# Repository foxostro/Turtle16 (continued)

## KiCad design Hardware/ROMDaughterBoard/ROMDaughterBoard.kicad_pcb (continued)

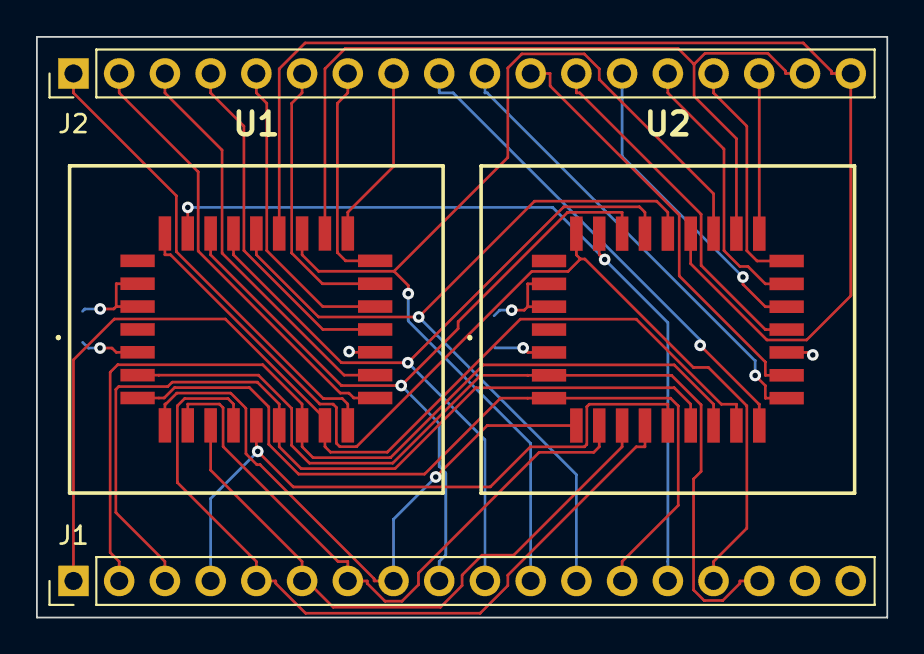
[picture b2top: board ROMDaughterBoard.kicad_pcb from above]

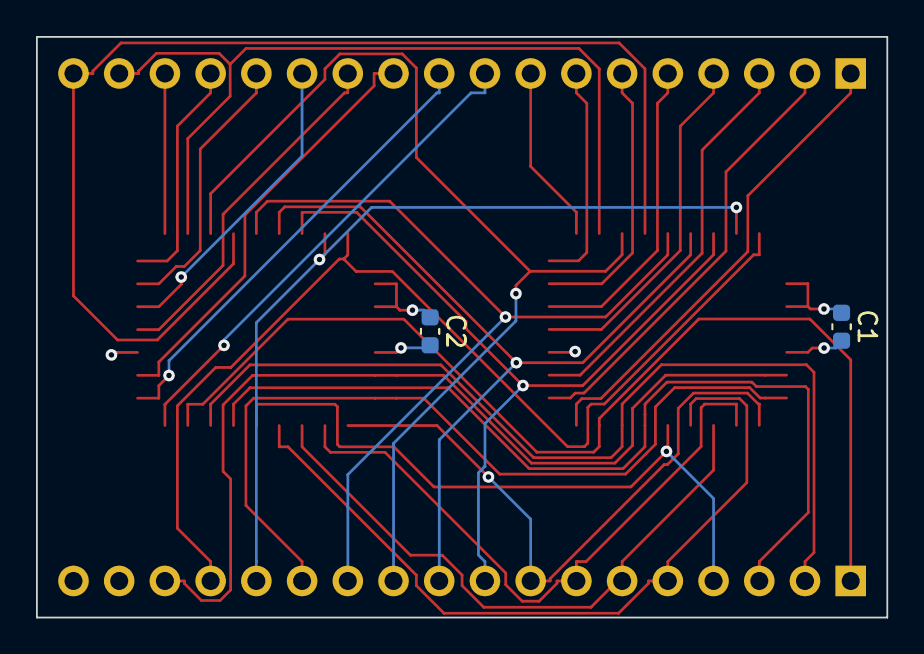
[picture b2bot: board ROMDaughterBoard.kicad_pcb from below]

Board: 4 copper layers, 47.2 x 32.3 mm, 6 parts (2 on the bottom side), 36 nets.

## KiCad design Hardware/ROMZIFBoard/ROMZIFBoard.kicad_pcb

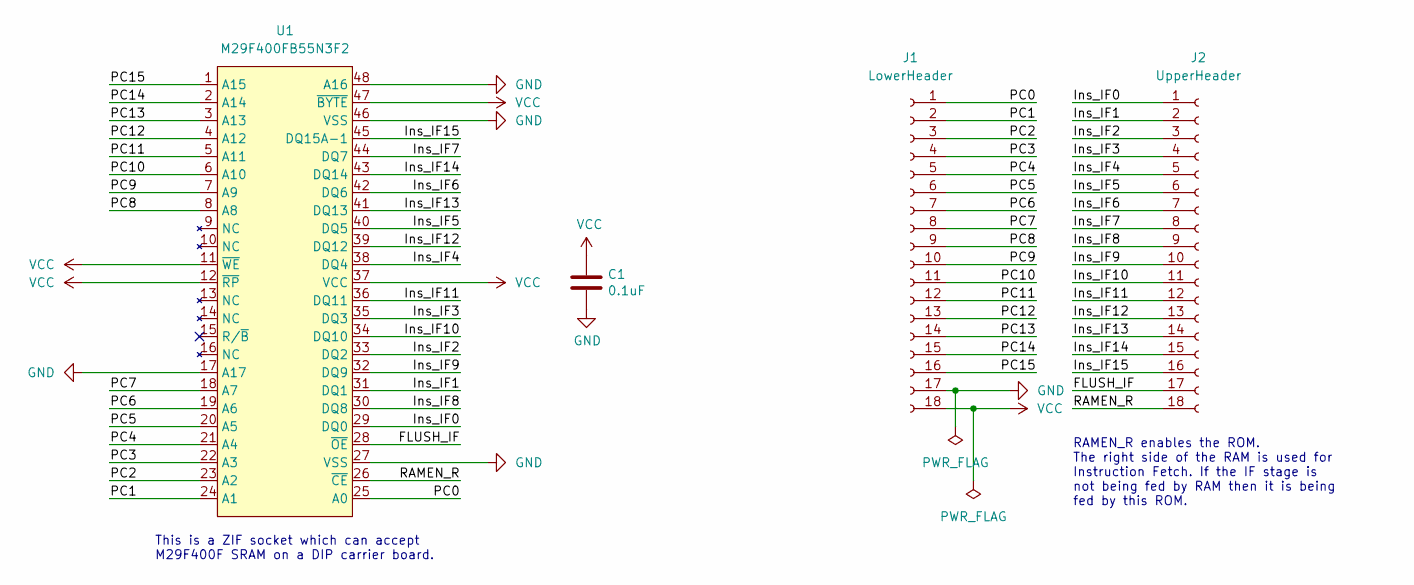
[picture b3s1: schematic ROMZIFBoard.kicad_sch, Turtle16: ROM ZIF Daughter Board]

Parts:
C1: 0.1uF; C_0603_1608Metric; Manufacturer# EMK107B7104KAHT; Mouser# 963-EMK107B7104KAHT
J1: LowerHeader; PinSocket_1x18_P2.54mm_Vertical
J2: UpperHeader; PinSocket_1x18_P2.54mm_Vertical
U1: M29F400FB55N3F2; DIP-48_W15.24mm_Socket; Manufacturer# 48-6554-10; Mouser# 535-48-6554-10

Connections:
/FLUSH_IF: J2.17, U1.28 (~OE)
/Ins_IF0: J2.1, U1.29 (DQ0)
/Ins_IF1: J2.2, U1.31 (DQ1)
/Ins_IF2: J2.3, U1.33 (DQ2)
/Ins_IF3: J2.4, U1.35 (DQ3)
/Ins_IF4: J2.5, U1.38 (DQ4)
/Ins_IF5: J2.6, U1.40 (DQ5)
/Ins_IF6: J2.7, U1.42 (DQ6)
/Ins_IF7: J2.8, U1.44 (DQ7)
/Ins_IF8: J2.9, U1.30 (DQ8)
/Ins_IF9: J2.10, U1.32 (DQ9)
/Ins_IF10: J2.11, U1.34 (DQ10)
/Ins_IF11: J2.12, U1.36 (DQ11)
/Ins_IF12: J2.13, U1.39 (DQ12)
/Ins_IF13: J2.14, U1.41 (DQ13)
/Ins_IF14: J2.15, U1.43 (DQ14)
/Ins_IF15: J2.16, U1.45 (DQ15A-1)
/PC0: J1.1, U1.25 (A0)
/PC1: J1.2, U1.24 (A1)
/PC2: J1.3, U1.23 (A2)
/PC3: J1.4, U1.22 (A3)
/PC4: J1.5, U1.21 (A4)
/PC5: J1.6, U1.20 (A5)
/PC6: J1.7, U1.19 (A6)
/PC7: J1.8, U1.18 (A7)
/PC8: J1.9, U1.8 (A8)
/PC9: J1.10, U1.7 (A9)
/PC10: J1.11, U1.6 (A10)
/PC11: J1.12, U1.5 (A11)
/PC12: J1.13, U1.4 (A12)
/PC13: J1.14, U1.3 (A13)
/PC14: J1.15, U1.2 (A14)
/PC15: J1.16, U1.1 (A15)
/RAMEN_R: J2.18, U1.26 (~CE)
GND: C1.2, J1.17, U1.17 (A17), U1.27 (VSS), U1.46 (VSS), U1.48 (A16)
VCC: C1.1, J1.18, U1.11 (~WE), U1.12 (~RP), U1.37 (VCC), U1.47 (~BYTE)

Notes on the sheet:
RAMEN_R enables the ROM. The right side of the RAM is used for Instruction Fetch. If the IF stage is not being fed by RAM then it is being fed by this ROM.
This is a ZIF socket which can accept M29F400F SRAM on a DIP carrier board.

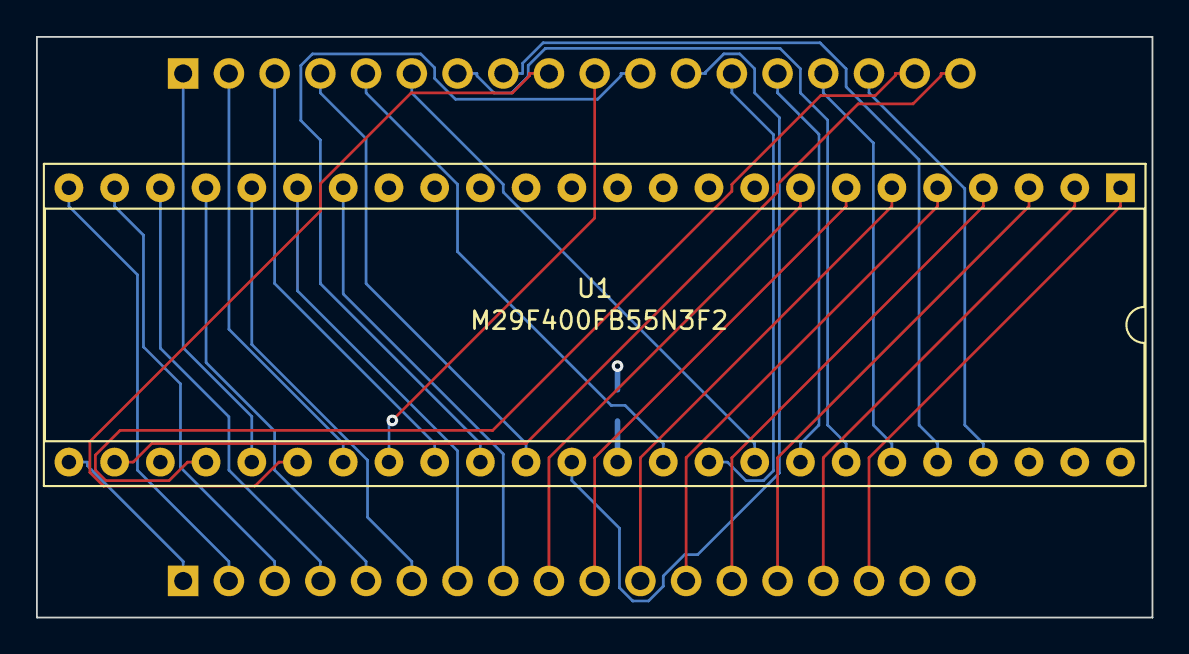
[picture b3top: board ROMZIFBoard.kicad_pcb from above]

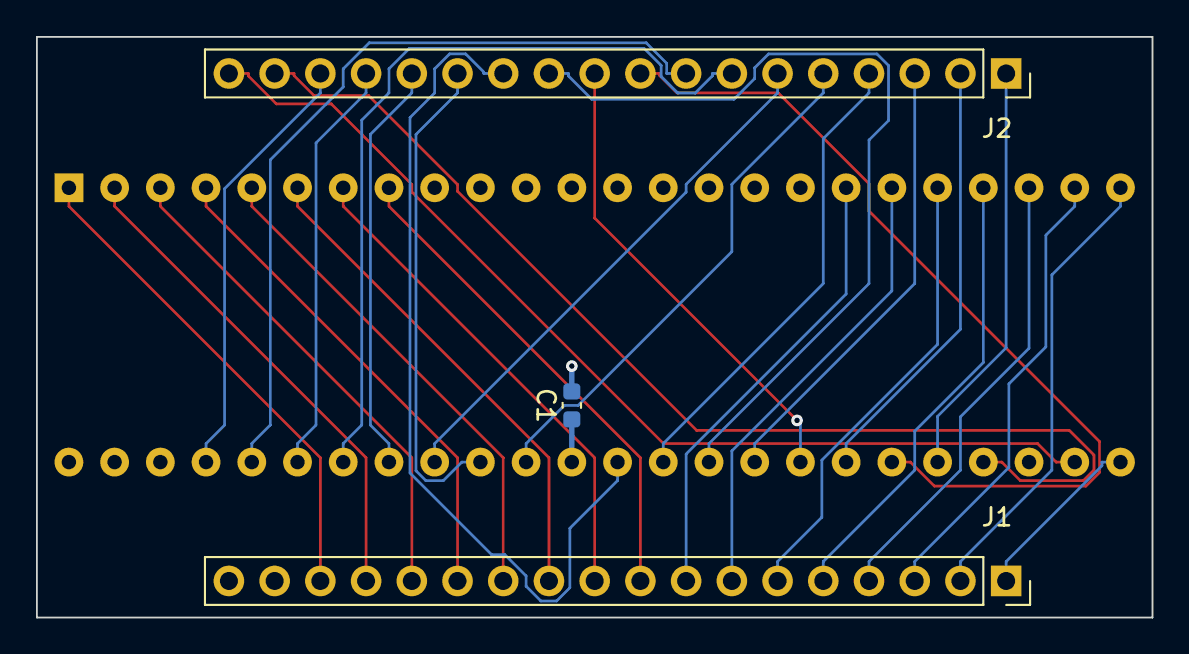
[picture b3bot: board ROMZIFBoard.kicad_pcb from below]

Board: 4 copper layers, 62.0 x 32.3 mm, 4 parts (3 on the bottom side), 36 nets.

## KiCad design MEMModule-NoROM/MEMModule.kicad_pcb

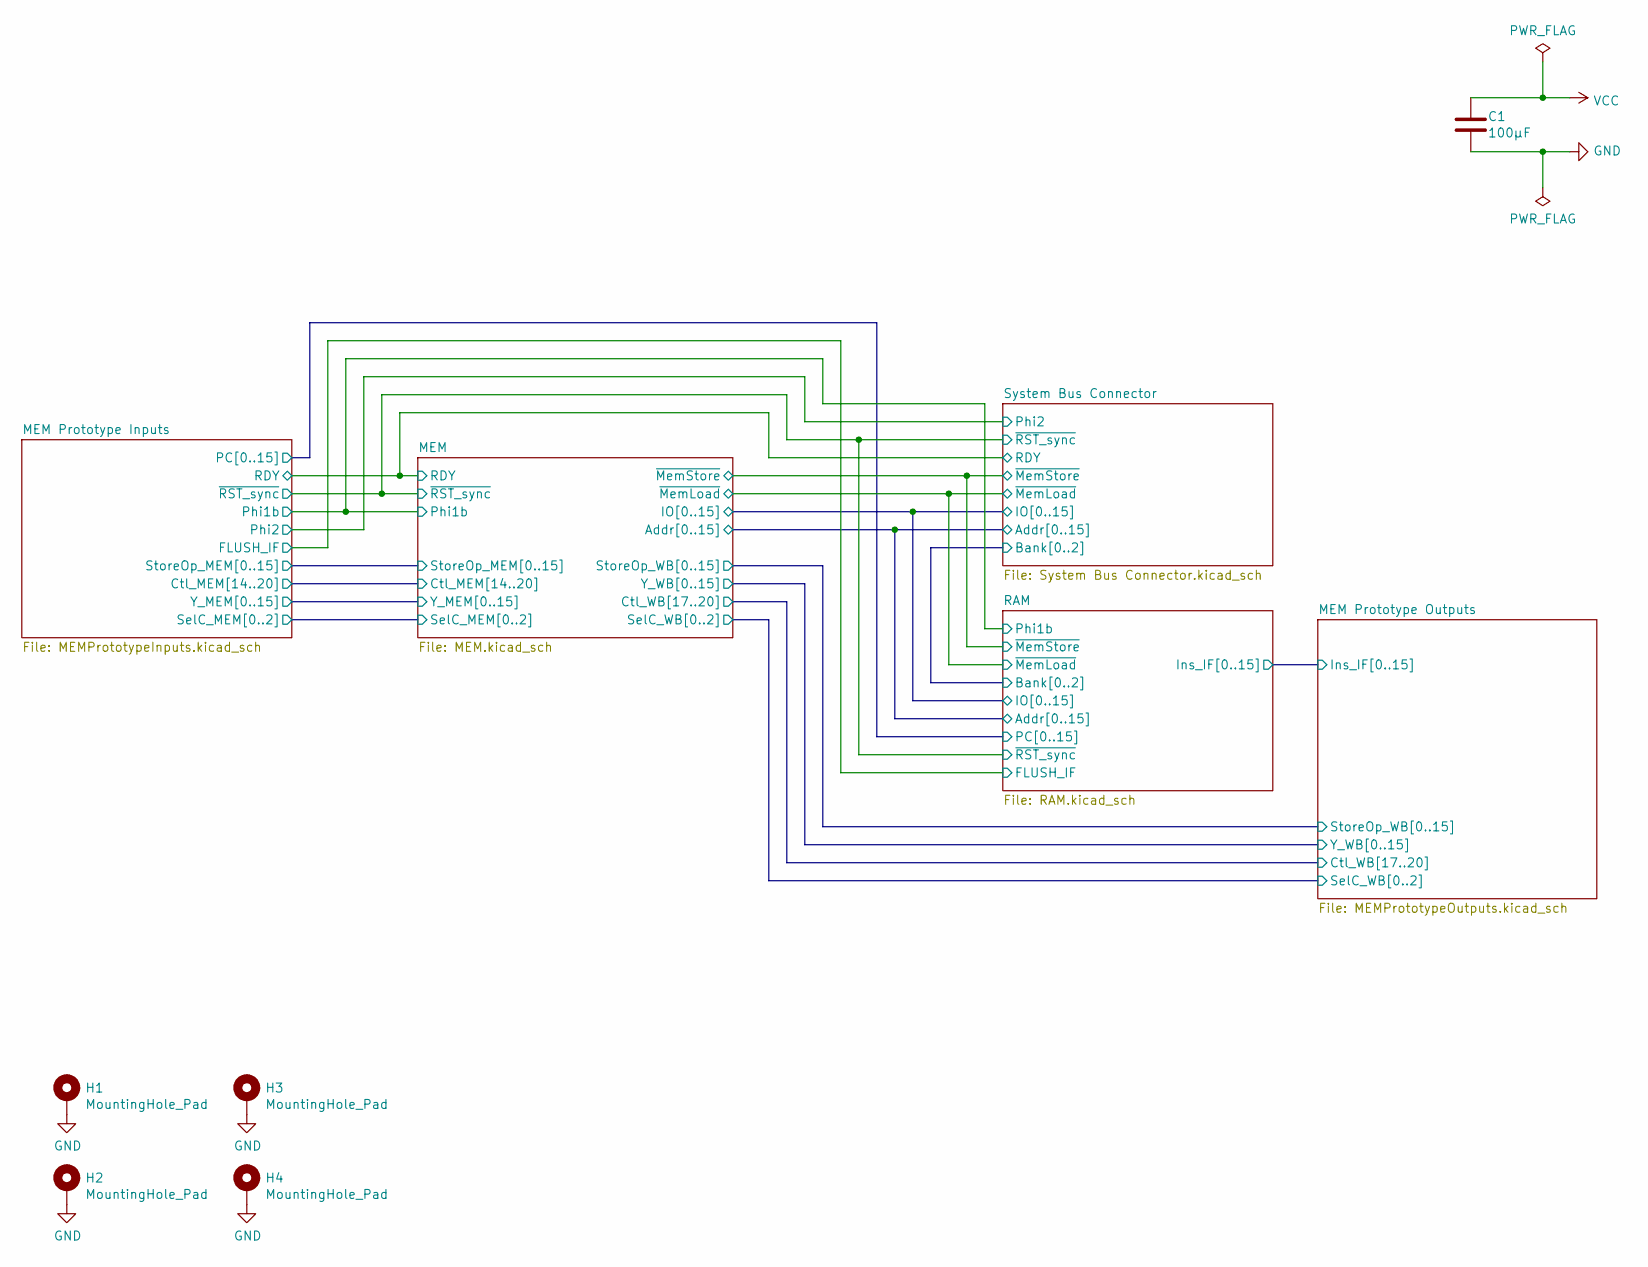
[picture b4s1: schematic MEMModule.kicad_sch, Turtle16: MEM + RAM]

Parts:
C1: 100µF; C_1206_3216Metric_Pad1.33x1.80mm_HandSolder
H1, H2, H3, H4: MountingHole_Pad; MountingHole_3.2mm_M3_Pad

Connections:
GND: C1.2, H1.1, H2.1, H3.1, H4.1; also elsewhere on the board
VCC: C1.1; also elsewhere on the board

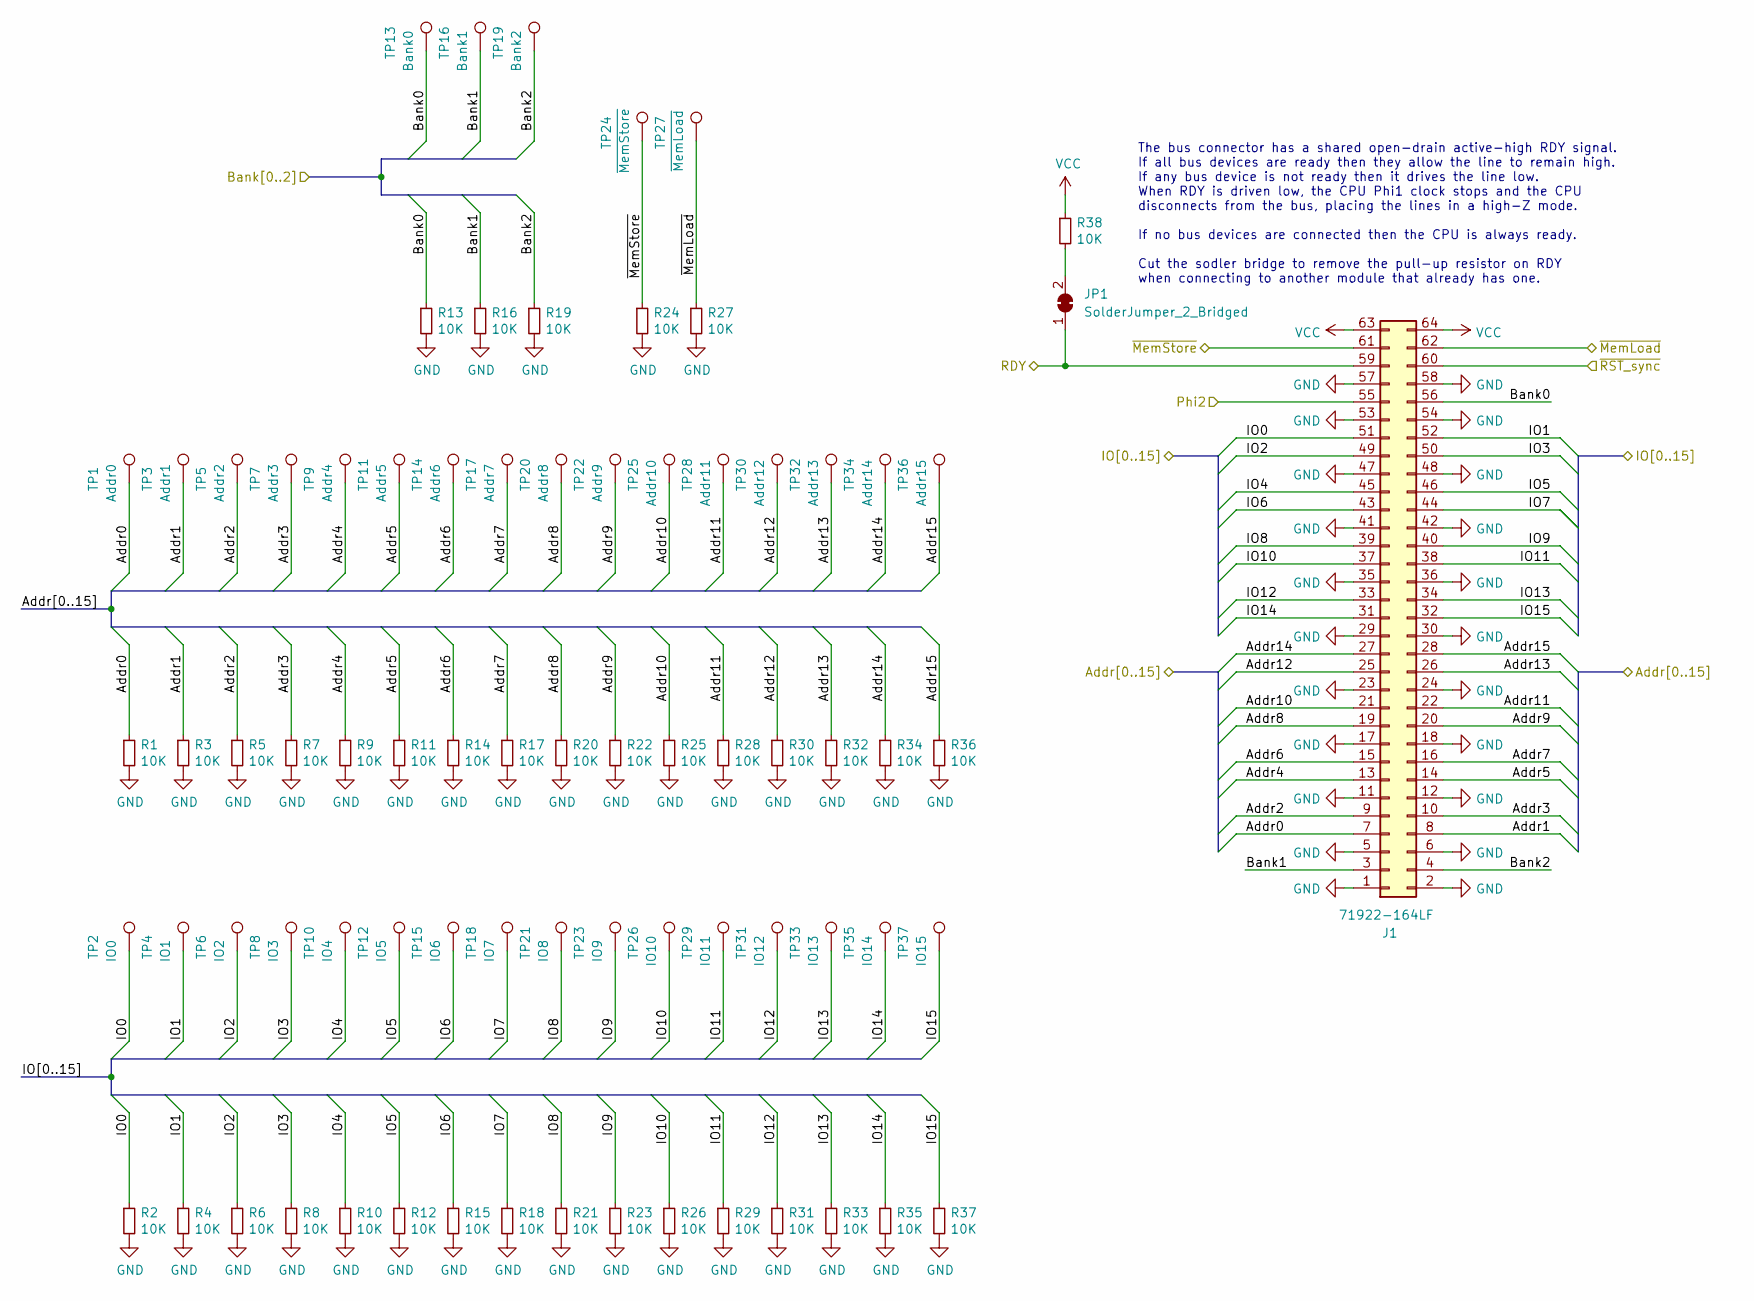
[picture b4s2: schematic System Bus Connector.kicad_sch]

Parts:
J1: 71922-164LF; IDC-Header_2x32_P2.54mm_Horizontal
JP1: SolderJumper_2_Bridged; SolderJumper-2_P1.3mm_Bridged_RoundedPad1.0x1.5mm
R1, R2, R3, R4, R5, R6, R7, R8, R9, R10, R11, R12, R13, R14, R15, R16, R17, R18, R19, R20, R21, R22, R23, R24, R25, R26, R27, R28, R29, R30, R31, R32, R33, R34, R35, R36, R37, R38: 10K; R_0603_1608Metric_Pad0.98x0.95mm_HandSolder
TP1: Addr0; TestPoint_Pad_D1.0mm
TP2: IO0; TestPoint_Pad_D1.0mm
TP3: Addr1; TestPoint_Pad_D1.0mm
TP4: IO1; TestPoint_Pad_D1.0mm
TP5: Addr2; TestPoint_Pad_D1.0mm
TP6: IO2; TestPoint_Pad_D1.0mm
TP7: Addr3; TestPoint_Pad_D1.0mm
TP8: IO3; TestPoint_Pad_D1.0mm
TP9: Addr4; TestPoint_Pad_D1.0mm
TP10: IO4; TestPoint_Pad_D1.0mm
TP11: Addr5; TestPoint_Pad_D1.0mm
TP12: IO5; TestPoint_Pad_D1.0mm
TP13: Bank0; TestPoint_Pad_D1.0mm
TP14: Addr6; TestPoint_Pad_D1.0mm
TP15: IO6; TestPoint_Pad_D1.0mm
TP16: Bank1; TestPoint_Pad_D1.0mm
TP17: Addr7; TestPoint_Pad_D1.0mm
TP18: IO7; TestPoint_Pad_D1.0mm
TP19: Bank2; TestPoint_Pad_D1.0mm
TP20: Addr8; TestPoint_Pad_D1.0mm
TP21: IO8; TestPoint_Pad_D1.0mm
TP22: Addr9; TestPoint_Pad_D1.0mm
TP23: IO9; TestPoint_Pad_D1.0mm
TP24: ~{MemStore}; TestPoint_Pad_D1.0mm
TP25: Addr10; TestPoint_Pad_D1.0mm
TP26: IO10; TestPoint_Pad_D1.0mm
TP27: ~{MemLoad}; TestPoint_Pad_D1.0mm
TP28: Addr11; TestPoint_Pad_D1.0mm
TP29: IO11; TestPoint_Pad_D1.0mm
TP30: Addr12; TestPoint_Pad_D1.0mm
TP31: IO12; TestPoint_Pad_D1.0mm
TP32: Addr13; TestPoint_Pad_D1.0mm
TP33: IO13; TestPoint_Pad_D1.0mm
TP34: Addr14; TestPoint_Pad_D1.0mm
TP35: IO14; TestPoint_Pad_D1.0mm
TP36: Addr15; TestPoint_Pad_D1.0mm
TP37: IO15; TestPoint_Pad_D1.0mm

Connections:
/MEM Prototype Inputs/Phi2: J1.55; also elsewhere on the board
/MEM Prototype Inputs/RDY: J1.59, JP1.1 (A); also elsewhere on the board
/MEM Prototype Inputs/~RST_sync: J1.60; also elsewhere on the board
/RAM/Addr0: J1.7, R1.1, TP1.1; also elsewhere on the board
/RAM/Addr1: J1.8, R3.1, TP3.1; also elsewhere on the board
/RAM/Addr2: J1.9, R5.1, TP5.1; also elsewhere on the board
/RAM/Addr3: J1.10, R7.1, TP7.1; also elsewhere on the board
/RAM/Addr4: J1.13, R9.1, TP9.1; also elsewhere on the board
/RAM/Addr5: J1.14, R11.1, TP11.1; also elsewhere on the board
/RAM/Addr6: J1.15, R14.1, TP14.1; also elsewhere on the board
/RAM/Addr7: J1.16, R17.1, TP17.1; also elsewhere on the board
/RAM/Addr8: J1.19, R20.1, TP20.1; also elsewhere on the board
/RAM/Addr9: J1.20, R22.1, TP22.1; also elsewhere on the board
/RAM/Addr10: J1.21, R25.1, TP25.1; also elsewhere on the board
/RAM/Addr11: J1.22, R28.1, TP28.1; also elsewhere on the board
/RAM/Addr12: J1.25, R30.1, TP30.1; also elsewhere on the board
/RAM/Addr13: J1.26, R32.1, TP32.1; also elsewhere on the board
/RAM/Addr14: J1.27, R34.1, TP34.1; also elsewhere on the board
/RAM/Addr15: J1.28, R36.1, TP36.1; also elsewhere on the board
/RAM/Bank0: J1.56, R13.1, TP13.1; also elsewhere on the board
/RAM/Bank1: J1.3, R16.1, TP16.1; also elsewhere on the board
/RAM/Bank2: J1.4, R19.1, TP19.1; also elsewhere on the board
/RAM/IO0: J1.51, R2.1, TP2.1; also elsewhere on the board
/RAM/IO1: J1.52, R4.1, TP4.1; also elsewhere on the board
/RAM/IO2: J1.49, R6.1, TP6.1; also elsewhere on the board
/RAM/IO3: J1.50, R8.1, TP8.1; also elsewhere on the board
/RAM/IO4: J1.45, R10.1, TP10.1; also elsewhere on the board
/RAM/IO5: J1.46, R12.1, TP12.1; also elsewhere on the board
/RAM/IO6: J1.43, R15.1, TP15.1; also elsewhere on the board
/RAM/IO7: J1.44, R18.1, TP18.1; also elsewhere on the board
/RAM/IO8: J1.39, R21.1, TP21.1; also elsewhere on the board
/RAM/IO9: J1.40, R23.1, TP23.1; also elsewhere on the board
/RAM/IO10: J1.37, R26.1, TP26.1; also elsewhere on the board
/RAM/IO11: J1.38, R29.1, TP29.1; also elsewhere on the board
/RAM/IO12: J1.33, R31.1, TP31.1; also elsewhere on the board
/RAM/IO13: J1.34, R33.1, TP33.1; also elsewhere on the board
/RAM/IO14: J1.31, R35.1, TP35.1; also elsewhere on the board
/RAM/IO15: J1.32, R37.1, TP37.1; also elsewhere on the board
/System Bus Connector/~MemLoad: J1.62, R27.1, TP27.1; also elsewhere on the board
/System Bus Connector/~MemStore: J1.61, R24.1, TP24.1; also elsewhere on the board
GND: J1.1, J1.2, J1.5, J1.6, J1.11, J1.12, J1.17, J1.18, J1.23, J1.24, J1.29, J1.30, J1.35, J1.36, J1.41, J1.42, J1.47, J1.48, J1.53, J1.54, J1.57, J1.58, R1.2, R2.2, R3.2, R4.2, R5.2, R6.2, R7.2, R8.2, R9.2, R10.2, R11.2, R12.2, R13.2, R14.2, R15.2, R16.2, R17.2, R18.2, R19.2, R20.2, R21.2, R22.2, R23.2, R24.2, R25.2, R26.2, R27.2, R28.2, R29.2, R30.2, R31.2, R32.2, R33.2, R34.2, R35.2, R36.2, R37.2; also elsewhere on the board
unnamed: JP1.2 (B), R38.2
VCC: J1.63, J1.64, R38.1; also elsewhere on the board

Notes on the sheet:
The bus connector has a shared open-drain active-high RDY signal. If all bus devices are ready then they allow the line to remain high. If any bus device is not ready then it drives the line low. When RDY is driven low, the CPU Phi1 clock stops and the CPU disconnects from the bus, placing the line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

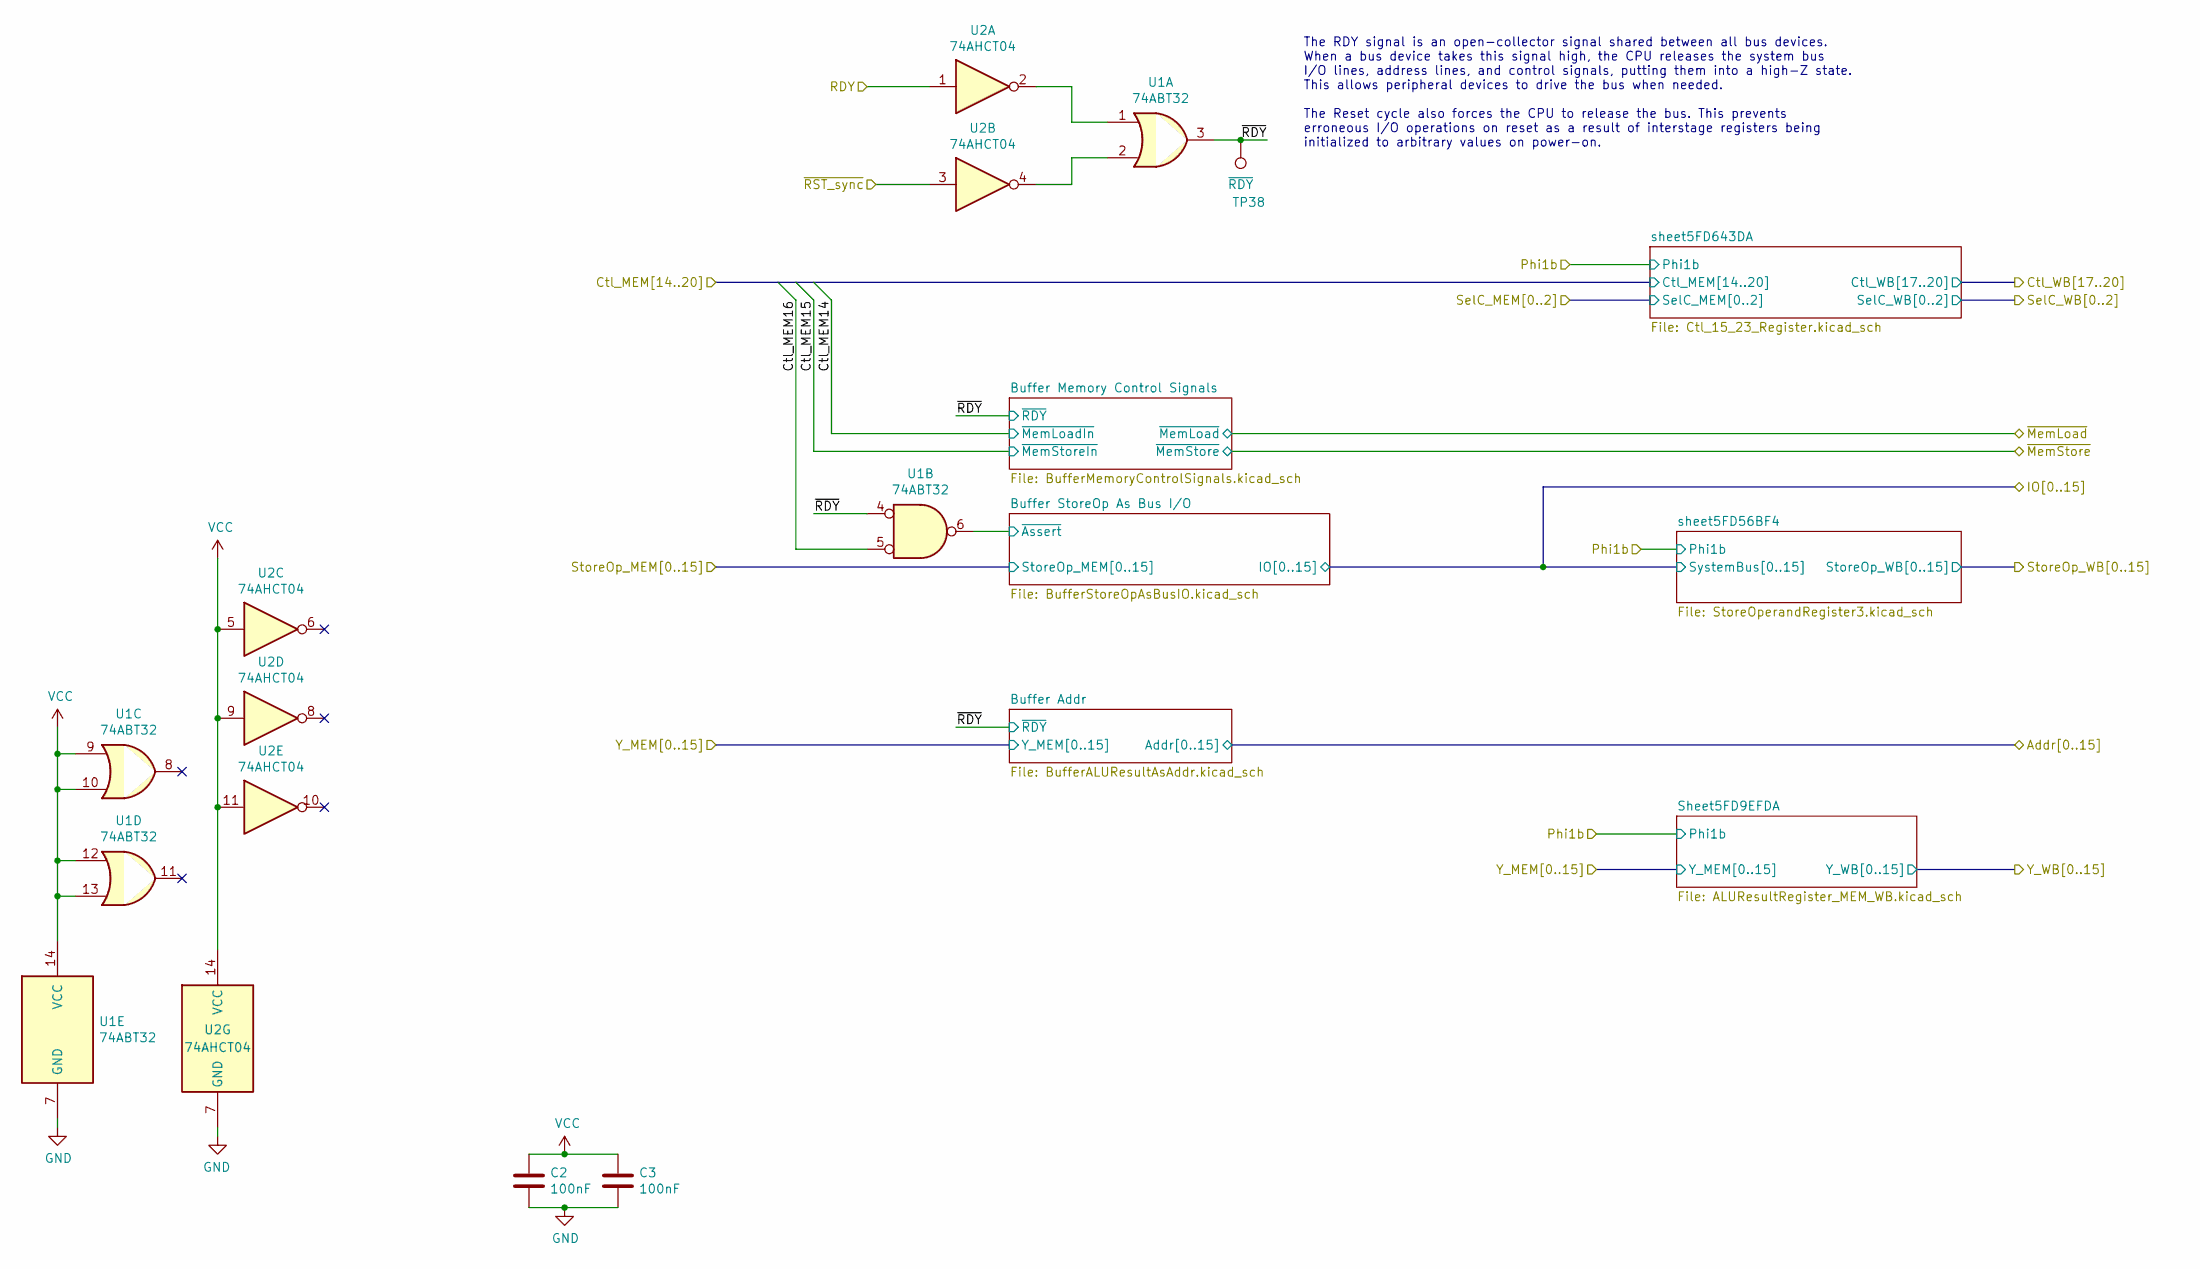
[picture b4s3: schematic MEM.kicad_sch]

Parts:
C2, C3: 100nF; C_0603_1608Metric_Pad1.08x0.95mm_HandSolder
TP38: ~{RDY}; TestPoint_Pad_D1.0mm
U1: 74ABT32; TSSOP-14_4.4x5mm_P0.65mm
U2: 74AHCT04; TSSOP-14_4.4x5mm_P0.65mm

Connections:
/MEM Prototype Inputs/Ctl_MEM16: U1.5; also elsewhere on the board
/MEM Prototype Inputs/RDY: U2.1; also elsewhere on the board
/MEM Prototype Inputs/~RST_sync: U2.3; also elsewhere on the board
/MEM/Buffer StoreOp As Bus I/O/~Assert: U1.6; also elsewhere on the board
/MEM/~RDY: TP38.1, U1.3, U1.4; also elsewhere on the board
GND: C2.2, C3.2, U1.7 (GND), U2.7 (GND); also elsewhere on the board
unnamed: U1.1, U2.2
unnamed: U1.2, U2.4
VCC: C2.1, C3.1, U1.9, U1.10, U1.12, U1.13, U1.14 (VCC), U2.5, U2.9, U2.11, U2.14 (VCC); also elsewhere on the board

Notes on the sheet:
The RDY signal is an open-collector signal shared between all bus devices. When a bus device takes this signal high, the CPU releases the system bus I/O lines, address lines, and control signals, putting them into a high-Z state. This allows peripheral devices to drive the bus when needed. The Rese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

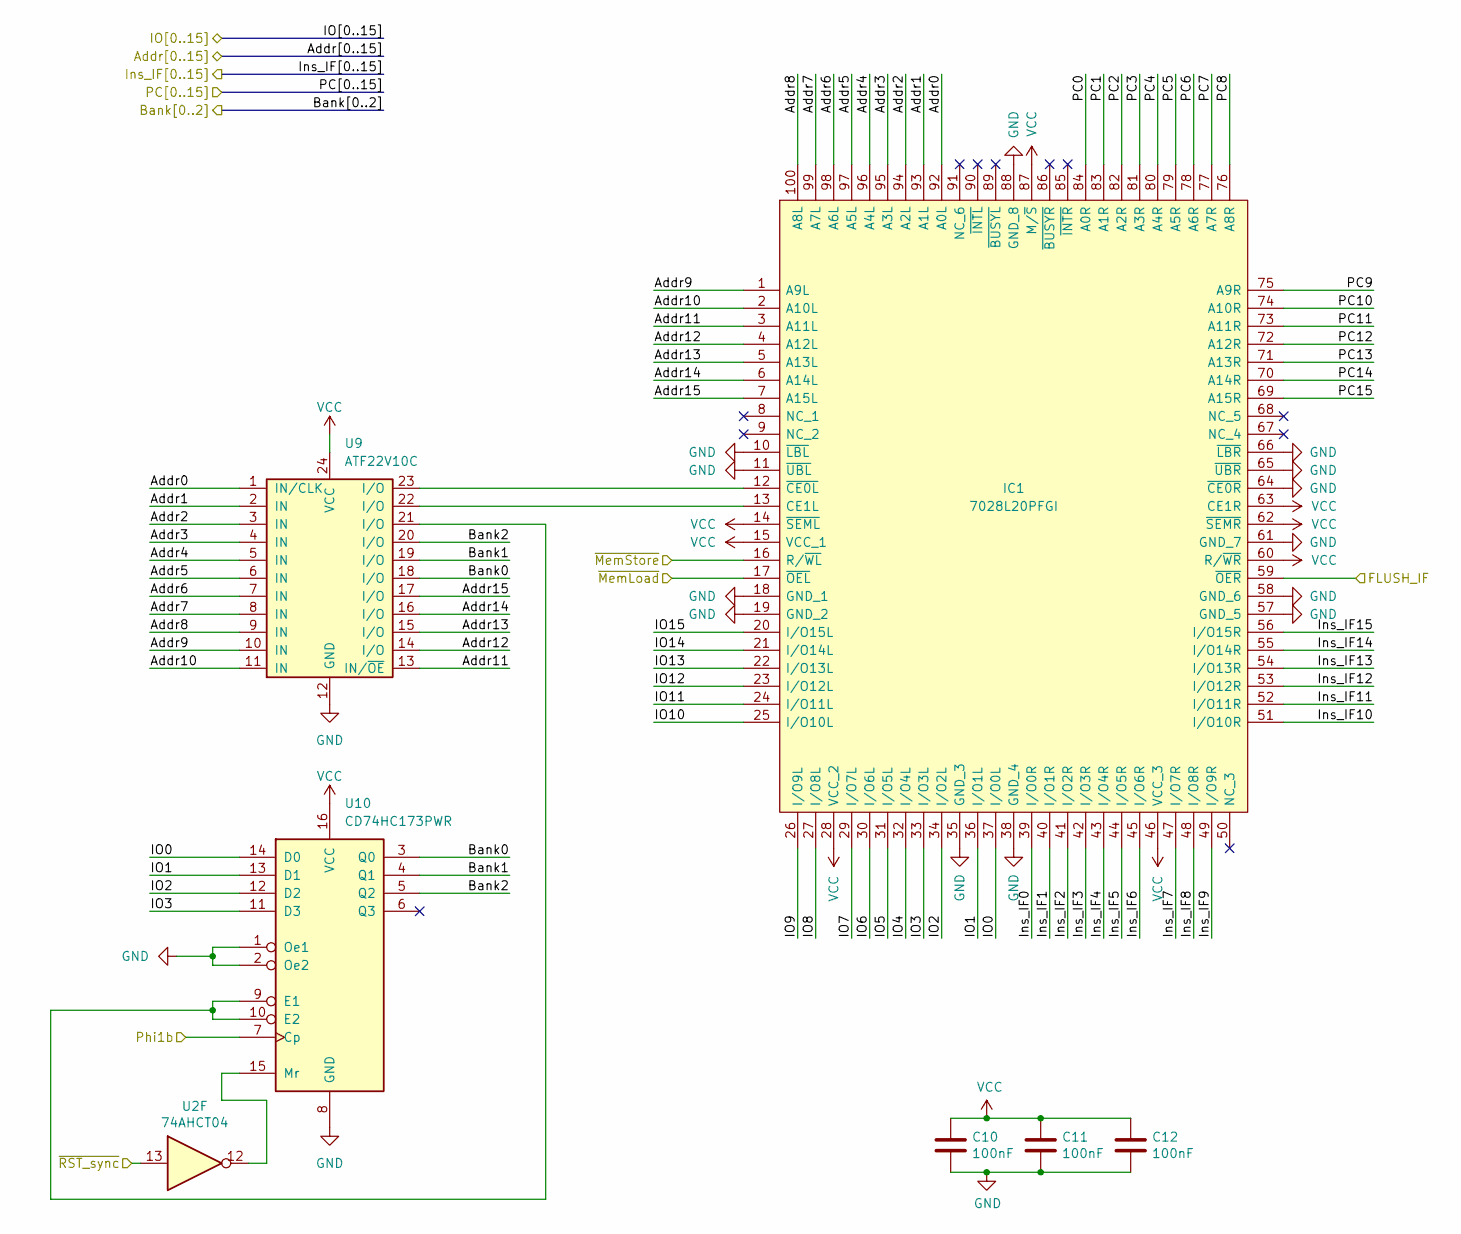
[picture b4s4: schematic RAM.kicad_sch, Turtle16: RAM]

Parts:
C10, C11, C12: 100nF; C_0603_1608Metric_Pad1.08x0.95mm_HandSolder
IC1: 7028L20PFGI; TQFP-100_14x14mm_P0.5mm; Manufacturer_Part_Number 7028L20PFGI; Mouser Part Number 972-7028L20PFGI
U2: 74AHCT04; TSSOP-14_4.4x5mm_P0.65mm
U9: ATF22V10C; DIP-24_W7.62mm_Socket
U10: CD74HC173PWR; TSSOP-16_4.4x5mm_P0.65mm

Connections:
/MEM Prototype Inputs/FLUSH_IF: IC1.59 (~OER); also elsewhere on the board
/MEM Prototype Inputs/Phi1b: U10.7 (Cp); also elsewhere on the board
/MEM Prototype Inputs/~RST_sync: U2.13; also elsewhere on the board
/RAM/Addr0: IC1.92 (A0L), U9.1 (IN/CLK); also elsewhere on the board
/RAM/Addr1: IC1.93 (A1L), U9.2 (IN); also elsewhere on the board
/RAM/Addr2: IC1.94 (A2L), U9.3 (IN); also elsewhere on the board
/RAM/Addr3: IC1.95 (A3L), U9.4 (IN); also elsewhere on the board
/RAM/Addr4: IC1.96 (A4L), U9.5 (IN); also elsewhere on the board
/RAM/Addr5: IC1.97 (A5L), U9.6 (IN); also elsewhere on the board
/RAM/Addr6: IC1.98 (A6L), U9.7 (IN); also elsewhere on the board
/RAM/Addr7: IC1.99 (A7L), U9.8 (IN); also elsewhere on the board
/RAM/Addr8: IC1.100 (A8L), U9.9 (IN); also elsewhere on the board
/RAM/Addr9: IC1.1 (A9L), U9.10 (IN); also elsewhere on the board
/RAM/Addr10: IC1.2 (A10L), U9.11 (IN); also elsewhere on the board
/RAM/Addr11: IC1.3 (A11L), U9.13 (IN/~OE); also elsewhere on the board
/RAM/Addr12: IC1.4 (A12L), U9.14 (I/O); also elsewhere on the board
/RAM/Addr13: IC1.5 (A13L), U9.15 (I/O); also elsewhere on the board
/RAM/Addr14: IC1.6 (A14L), U9.16 (I/O); also elsewhere on the board
/RAM/Addr15: IC1.7 (A15L), U9.17 (I/O); also elsewhere on the board
/RAM/Bank0: U9.18 (I/O), U10.3 (Q0); also elsewhere on the board
/RAM/Bank1: U9.19 (I/O), U10.4 (Q1); also elsewhere on the board
/RAM/Bank2: U9.20 (I/O), U10.5 (Q2); also elsewhere on the board
/RAM/IO0: IC1.37 (I/O0L), U10.14 (D0); also elsewhere on the board
/RAM/IO1: IC1.36 (I/O1L), U10.13 (D1); also elsewhere on the board
/RAM/IO2: IC1.34 (I/O2L), U10.12 (D2); also elsewhere on the board
/RAM/IO3: IC1.33 (I/O3L), U10.11 (D3); also elsewhere on the board
/RAM/IO4: IC1.32 (I/O4L); also elsewhere on the board
/RAM/IO5: IC1.31 (I/O5L); also elsewhere on the board
/RAM/IO6: IC1.30 (I/O6L); also elsewhere on the board
/RAM/IO7: IC1.29 (I/O7L); also elsewhere on the board
/RAM/IO8: IC1.27 (I/O8L); also elsewhere on the board
/RAM/IO9: IC1.26 (I/O9L); also elsewhere on the board
/RAM/IO10: IC1.25 (I/O10L); also elsewhere on the board
/RAM/IO11: IC1.24 (I/O11L); also elsewhere on the board
/RAM/IO12: IC1.23 (I/O12L); also elsewhere on the board
/RAM/IO13: IC1.22 (I/O13L); also elsewhere on the board
/RAM/IO14: IC1.21 (I/O14L); also elsewhere on the board
/RAM/IO15: IC1.20 (I/O15L); also elsewhere on the board
/RAM/Ins_IF0: IC1.39 (I/O0R); also elsewhere on the board
/RAM/Ins_IF1: IC1.40 (I/O1R); also elsewhere on the board
/RAM/Ins_IF2: IC1.41 (I/O2R); also elsewhere on the board
/RAM/Ins_IF3: IC1.42 (I/O3R); also elsewhere on the board
/RAM/Ins_IF4: IC1.43 (I/O4R); also elsewhere on the board
/RAM/Ins_IF5: IC1.44 (I/O5R); also elsewhere on the board
/RAM/Ins_IF6: IC1.45 (I/O6R); also elsewhere on the board
/RAM/Ins_IF7: IC1.47 (I/O7R); also elsewhere on the board
/RAM/Ins_IF8: IC1.48 (I/O8R); also elsewhere on the board
/RAM/Ins_IF9: IC1.49 (I/O9R); also elsewhere on the board
/RAM/Ins_IF10: IC1.51 (I/O10R); also elsewhere on the board
/RAM/Ins_IF11: IC1.52 (I/O11R); also elsewhere on the board
/RAM/Ins_IF12: IC1.53 (I/O12R); also elsewhere on the board
/RAM/Ins_IF13: IC1.54 (I/O13R); also elsewhere on the board
/RAM/Ins_IF14: IC1.55 (I/O14R); also elsewhere on the board
/RAM/Ins_IF15: IC1.56 (I/O15R); also elsewhere on the board
/RAM/PC0: IC1.84 (A0R); also elsewhere on the board
/RAM/PC1: IC1.83 (A1R); also elsewhere on the board
/RAM/PC2: IC1.82 (A2R); also elsewhere on the board
/RAM/PC3: IC1.81 (A3R); also elsewhere on the board
/RAM/PC4: IC1.80 (A4R); also elsewhere on the board
/RAM/PC5: IC1.79 (A5R); also elsewhere on the board
/RAM/PC6: IC1.78 (A6R); also elsewhere on the board
/RAM/PC7: IC1.77 (A7R); also elsewhere on the board
/RAM/PC8: IC1.76 (A8R); also elsewhere on the board
/RAM/PC9: IC1.75 (A9R); also elsewhere on the board
/RAM/PC10: IC1.74 (A10R); also elsewhere on the board
/RAM/PC11: IC1.73 (A11R); also elsewhere on the board
/RAM/PC12: IC1.72 (A12R); also elsewhere on the board
/RAM/PC13: IC1.71 (A13R); also elsewhere on the board
/RAM/PC14: IC1.70 (A14R); also elsewhere on the board
/RAM/PC15: IC1.69 (A15R); also elsewhere on the board
/System Bus Connector/~MemLoad: IC1.17 (~OEL); also elsewhere on the board
/System Bus Connector/~MemStore: IC1.16 (R/~WL); also elsewhere on the board
GND: C10.2, C11.2, C12.2, IC1.10 (~LBL), IC1.11 (~UBL), IC1.18 (GND_1), IC1.19 (GND_2), IC1.35 (GND_3), IC1.38 (GND_4), IC1.57 (GND_5), IC1.58 (GND_6), IC1.61 (GND_7), IC1.64 (~CE0R), IC1.65 (~UBR), IC1.66 (~LBR), IC1.88 (GND_8), U9.12 (GND), U10.1 (Oe1), U10.2 (Oe2), U10.8 (GND); also elsewhere on the board
unnamed: IC1.13 (CE1L), U9.22 (I/O)
unnamed: IC1.12 (~CE0L), U9.23 (I/O)
unnamed: U9.21 (I/O), U10.9 (E1), U10.10 (E2)
unnamed: U2.12, U10.15 (Mr)
VCC: C10.1, C11.1, C12.1, IC1.14 (~SEML), IC1.15 (VCC_1), IC1.28 (VCC_2), IC1.46 (VCC_3), IC1.60 (R/~WR), IC1.62 (~SEMR), IC1.63 (CE1R), IC1.87 (M/~S), U9.24 (VCC), U10.16 (VCC); also elsewhere on the board
